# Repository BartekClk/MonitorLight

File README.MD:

# MonitorLight — ATtiny85 Desk Lamp Controller

[-blue?logo=c)](https://www.microchip.com/)
[-lightgrey)](https://www.microchip.com/en-us/product/attiny85)

A compact, hardware desk lamp (screenbar) controller designed for monitor mounting. The project combines dedicated power regulation using a synchronous step-down converter, an incremental rotary encoder UI, and deterministic pure C firmware without Arduino runtime overhead.

---

## Key Features

* **Silent Power Stage (Fast PWM 31.25 kHz):** Operating well above the human audible spectrum (20 Hz – 20 kHz) eliminates inductor whine and ceramic capacitor piezo singing while avoiding camera sensor flicker.
* **Hardware Eye Perception (CIE 1931 Gamma Curve):** 32-step nonlinear lookup table stored in `PROGMEM` providing perceptually uniform brightness adjustments across the entire range.
* **True 0% PWM Standby:** Explicitly disconnects the timer output compare pin when turned off, eliminating residual sub-microsecond voltage spikes typical of AVR Fast PWM and preventing LED glow in standby.
* **Bounce-Immune Quadrature Decoding:** 16-state transition table state machine eliminates mechanical encoder bounce (EC11) without requiring external RC filter networks.
* **EEPROM Wear-Leveling Protection:** Current brightness level is committed to EEPROM only after 2 seconds of inactivity, drastically extending non-volatile cell endurance.
* **Soft-Fade Transition:** Smooth duty cycle ramping during power toggling and manual step adjustments.

---

## Hardware Architecture

| Component | Part / Value | Role in Circuit |
| :--- | :--- | :--- |
| **MCU** | `ATtiny85-20SU` (SOIC-8) | Main microcontroller (8 MHz internal, BOD 2.7V) |
| **Buck Regulator** | `AP63205WU-7` (TSOT-26) | Logic power rail: 12V → 5V (2A, 1.1 MHz) |
| **Switching MOSFET** | `IRLR024N` (TO-252) | Logic-level N-MOSFET Low-Side switch for 12V LED load |
| **Rotary Encoder** | `EC11E20-20P20C-SW` | User interface (20 PPR / 20 detents + momentary push button) |
| **Programming Port** | `J_ISP` (Pin Header) | Dedicated AVR ISP programming header |

### Pinout Configuration

```text
                  ┌───────[ ATtiny85 ]───────┐
      RESET (PB5) │ 1 [•]                  8 │ VCC (+5V AP63205)
   ENC_CLK  (PB3) │ 2                      7 │ PB2 (SCK / Unused)
   ENC_DT   (PB4) │ 3                      6 │ PB1 (ENC_SW - Pushbutton)
              GND │ 4                      5 │ PB0 (PWM -> MOSFET Gate)
                  └──────────────────────────┘
```

---

## Firmware State Machine

```mermaid
stateDiagram-v2
    [*] --> Standby: 12V Power Applied (Default OFF)
    
    Standby --> Active: Push Button (SW)
    note right of Active
      Soft-fade to saved
      brightness from EEPROM
    end note

    Standby --> Active: Rotate Clockwise (CW)
    note left of Standby
      Wake-up from minimum level (1)
    end note

    Active --> Active: Rotate Encoder (Step +/- along CIE1931)
    Active --> Standby: Push Button (SW / Soft-fade to 0)
    
    state Active {
        [*] --> Running
        Running --> EEPROM_Pending: Brightness Changed
        EEPROM_Pending --> Running: Commit after 2s inactivity
    }
```

---

## Repository Structure

```text
MonitorLight/
├── MonitorLight.kicad_sch   # KiCad schematic
├── MonitorLight.kicad_pcb   # Single-layer PCB layout
├── MonitorLight.kicad_pro   # KiCad project file
├── MonitorLight_Code/       # Firmware directory (PlatformIO)
│   ├── src/
│   │   └── main.c           # Pure C firmware (AVR-GCC)
│   ├── diagram.json         # Wokwi simulation circuit configuration
│   ├── wokwi.toml           # Wokwi VS Code integration settings
│   └── platformio.ini       # PlatformIO build configuration & fuse settings
├── .gitignore               # Repository hygiene rules
└── README.md
```

---

## Getting Started & Simulation

### Prerequisites
* [Visual Studio Code](https://code.visualstudio.com/)
* **PlatformIO IDE** extension
* **Wokwi Simulator** extension

### Local Build and Simulation
1. Clone the repository:
   ```bash
   git clone [https://github.com/](https://github.com/)<your-username>/MonitorLight.git
   ```
2. Open the `MonitorLight_Code` directory in VS Code.
3. Build the binary:
   ```bash
   pio run
   ```
4. Open `diagram.json`, open the command palette (`F1`), and execute:
   ```text
   Wokwi: Start Simulator
   ```
   *Rotate the encoder with the mouse, test button presses, and inspect real-time signal waveforms in the generated `wokwi.vcd` trace using extensions like VaporView.*

---

## Hardware Flashing

Flashing the physical board requires a standard **USBasp** programmer connected to the `J_ISP` header:

1. Burn fuse bits (Internal 8 MHz oscillator, BOD enabled at 2.7V):
   ```bash
   pio run -t fuses
   ```
   * Target values: `lfuse: 0xE2`, `hfuse: 0xDD`, `efuse: 0xFF`
2. Upload firmware via ISP:
   ```bash
   pio run -t upload
   ```

---

## License

This project is licensed under the MIT License — see the `LICENSE` file for details.

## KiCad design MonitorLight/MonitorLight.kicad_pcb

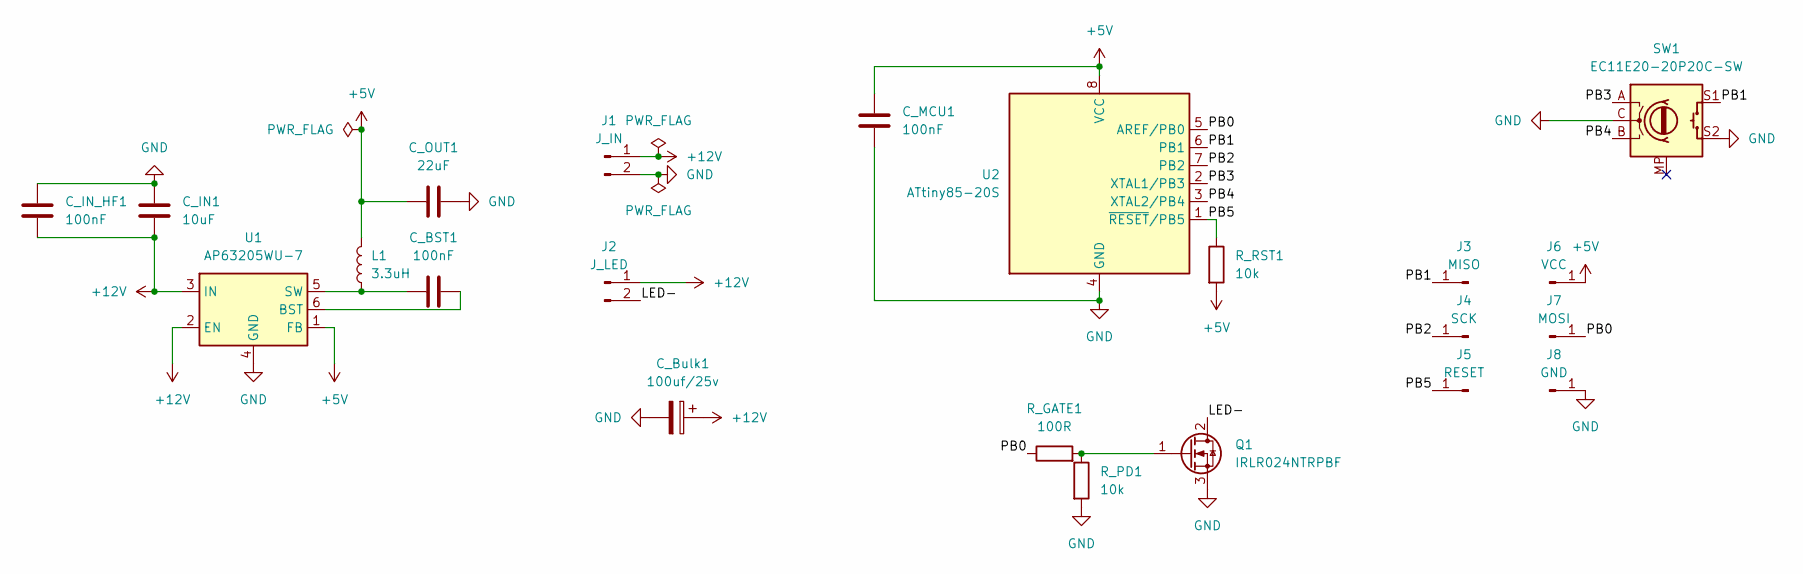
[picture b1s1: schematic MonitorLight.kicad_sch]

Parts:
C_BST1: 100nF; C_0805_2012Metric
C_Bulk1: 100uf/25v; C_Radial_D6.3mm_H11.0mm_P2.50mm
C_IN1: 10uF; C_0805_2012Metric
C_IN_HF1: 100nF; C_0805_2012Metric
C_MCU1: 100nF; C_0805_2012Metric
C_OUT1: 22uF; C_0805_2012Metric
J1: J_IN; SolderPads_01x02_M
J2: J_LED; SolderPads_01x02_M
J3: MISO; InspectionPads_01
J4: SCK; InspectionPads_01
J5: RESET; InspectionPads_01
J6: VCC; InspectionPads_01
J7: MOSI; InspectionPads_01
J8: GND; InspectionPads_01
L1: 3.3uH; L_Taiyo-Yuden_MD-2020
Q1: IRLR024NTRPBF
R_GATE1: 100R; R_0805_2012Metric
R_PD1: 10k; R_0805_2012Metric
R_RST1: 10k; R_0805_2012Metric
SW1: EC11E20-20P20C-SW; RotaryEncoder_Alps_EC11E-Switch_Vertical_H20mm_CircularMoun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
U1: AP63205WU-7; TSOT-23-6
U2: ATtiny85-20S; SOIC-8_5.3x5.3mm_P1.27mm

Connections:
+5V: C_MCU1.1, C_OUT1.1, J6.1 (Pin_1_1), L1.2, R_RST1.2, U1.1 (FB), U2.8 (VCC)
+12V: C_Bulk1.1, C_IN1.2, C_IN_HF1.2, J1.1, J2.1, U1.2 (EN), U1.3 (IN)
/LED-: J2.2, Q1.2 (D)
/PB0: J7.1 (Pin_1_1), R_GATE1.1, U2.5 (AREF/PB0)
/PB1: J3.1 (Pin_1_1), SW1.S1, U2.6 (PB1)
/PB2: J4.1 (Pin_1_1), U2.7 (PB2)
/PB3: SW1.A, U2.2 (XTAL1/PB3)
/PB4: SW1.B, U2.3 (XTAL2/PB4)
/PB5: J5.1 (Pin_1_1), R_RST1.1, U2.1 (~RESET/PB5)
GND: C_Bulk1.2, C_IN1.1, C_IN_HF1.1, C_MCU1.2, C_OUT1.2, J1.2, J8.1 (Pin_1_1), Q1.3 (S), R_PD1.2, SW1.C, SW1.S2, U1.4 (GND), U2.4 (GND)
unnamed: Q1.1 (G), R_GATE1.2, R_PD1.1
unnamed: C_BST1.2, U1.6 (BST)
unnamed: C_BST1.1, L1.1, U1.5 (SW)

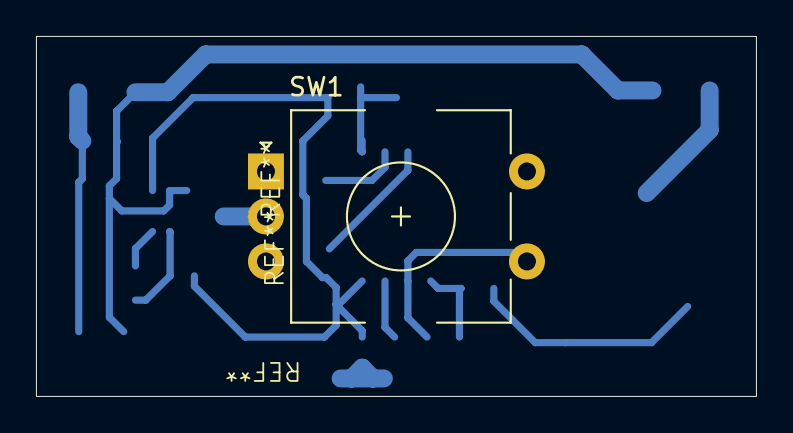
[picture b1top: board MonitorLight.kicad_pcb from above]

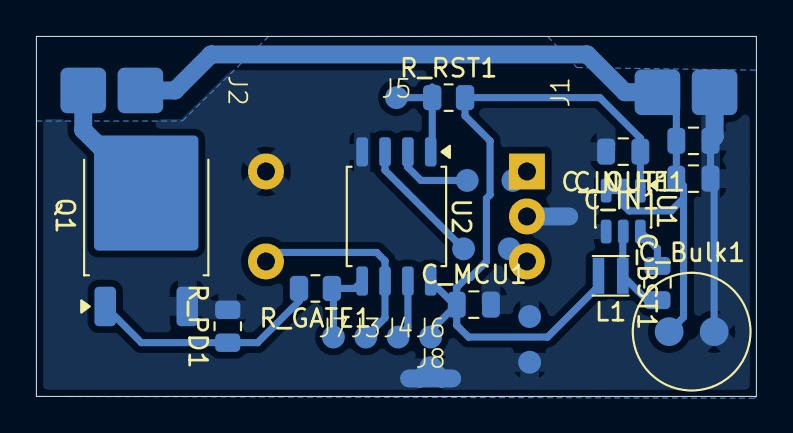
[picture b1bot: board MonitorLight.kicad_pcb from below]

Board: 2 copper layers, 40.0 x 20.0 mm, 22 parts (21 on the bottom side), 13 nets.

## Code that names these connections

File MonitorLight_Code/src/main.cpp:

#define F_CPU 8000000UL

#include <avr/io.h>
#include <avr/interrupt.h>
#include <avr/pgmspace.h>
#include <avr/eeprom.h>
#include <avr/power.h>
#include <stdbool.h>

// --- DEFINICJE PINÓW ---
#define PIN_PWM     PB0  // Pin 5: Wyjście PWM (OC0A)
#define PIN_ENC_SW  PB1  // Pin 6: Przycisk enkodera (SW)
#define PIN_ENC_A   PB3  // Pin 2: Enkoder A (CLK)
#define PIN_ENC_B   PB4  // Pin 3: Enkoder B (DT)

// --- PARAMETRY REGULACJI ---
#define BRIGHTNESS_STEPS 32
#define FADE_INTERVAL_MS 2     // Czas między krokami płynnego przejścia (2 ms)
#define EEPROM_DELAY_MS  2000  // Zapis do EEPROM po 2 s bezczynności

// Tablica korekcji gamma CIE1931 (32 kroki jasności)
static const uint8_t PROGMEM gamma_lut[BRIGHTNESS_STEPS] = {
      1,   2,   3,   4,   6,   8,  10,  13,
     16,  20,  25,  30,  36,  43,  51,  60,
     70,  81,  93, 106, 120, 136, 153, 171,
    190, 210, 232, 255, 255, 255, 255, 255
};

// Tablica przejść kwadraturowych enkodera (eliminuje drgania styków)
static const int8_t PROGMEM enc_table[16] = {
     0, -1,  1,  0,
     1,  0,  0, -1,
    -1,  0,  0,  1,
     0,  1, -1,  0
};

// Adresy EEPROM
#define EEPROM_MAGIC_ADDR 0x00
#define EEPROM_LEVEL_ADDR 0x01
#define EEPROM_MAGIC_KEY  0xA5

// --- ZMIENNE WSPÓŁDZIELONE Z PRZERWANIEM ---
volatile int8_t  g_enc_delta   = 0;
volatile bool    g_btn_pressed = false;
volatile bool    g_tick_1ms    = false;

// --- OBSŁUGA PWM (Timer0 - 31.25 kHz) ---
static void pwm_init(void) {
    DDRB |= (1 << PIN_PWM);
    PORTB &= ~(1 << PIN_PWM);

    // Tryb Fast PWM (WGM01 | WGM00), preskaler = 1 (CS00)
    TCCR0A = (1 << WGM01) | (1 << WGM00);
    TCCR0B = (1 << CS00);
    OCR0A  = 0;
}

static void pwm_set(uint8_t duty) {
    if (duty == 0) {
        // Odłącz wyjście OC0A, aby uniknąć szpilki przy OCR0A = 0
        TCCR0A &= ~(1 << COM0A1);
        PORTB  &= ~(1 << PIN_PWM);
    } else {
        OCR0A   = duty;
        TCCR0A |= (1 << COM0A1);
    }
}

// --- BAZA CZASU 1 ms (Timer1) ---
static void timer1_init(void) {
    // Tryb CTC, preskaler = 64 -> 8 MHz / 64 = 125 kHz
    // 125 impulsów (OCR1C = 124) daje przerwanie dokładnie co 1 ms (1 kHz)
    TCCR1  = (1 << CTC1) | (1 << CS12) | (1 << CS11) | (1 << CS10);
    OCR1C  = 124;
    OCR1A  = 124;
    TIMSK |= (1 << OCIE1A);
}

// --- PRZERWANIE CO 1 ms: ODCZYT ENKODERA I PRZYCISKU ---
ISR(TIMER1_COMPA_vect) {
    g_tick_1ms = true;

    // 1. Dekodowanie kwadraturowe enkodera
    static uint8_t prev_ab    = 0x03;
    static int8_t  substep    = 0;

    uint8_t pin_state = PINB;
    uint8_t curr_ab   = 0;
    if (pin_state & (1 << PIN_ENC_A)) curr_ab |= 0x02;
    if (pin_state & (1 << PIN_ENC_B)) curr_ab |= 0x01;

    if (curr_ab != prev_ab) {
        uint8_t idx = (prev_ab << 2) | curr_ab;
        substep += (int8_t)pgm_read_byte(&enc_table[idx]);
        prev_ab = curr_ab;

        // Zarejestruj krok w pełnej pozycji spoczynkowej (oba wejścia w stanie wysokim)
        if (curr_ab == 0x03) {
            if (substep >= 2) {
                g_enc_delta++;
            } else if (substep <= -2) {
                g_enc_delta--;
            }
            substep = 0;
        }
    }

    // 2. Debouncing przycisku SW (filtr 25 ms)
    static uint8_t btn_cnt     = 0;
    static bool    btn_latched = false;

    if (!(pin_state & (1 << PIN_ENC_SW))) {
        if (btn_cnt < 25) {
            btn_cnt++;
            if (btn_cnt == 25 && !btn_latched) {
                g_btn_pressed = true;
                btn_latched   = true;
            }
        }
    } else {
        btn_cnt     = 0;
        btn_latched = false;
    }
}

// --- PĘTLA GŁÓWNA ---
int main(void) {
    // Wymuś taktowanie 8 MHz (wyłącza podział zegara CKDIV8)
    clock_prescale_set(clock_div_1);

    // Piny enkodera i przycisku jako wejścia z wewnętrznym podciąganiem Pull-Up
    DDRB  &= ~((1 << PIN_ENC_A) | (1 << PIN_ENC_B) | (1 << PIN_ENC_SW));
    PORTB |=  ((1 << PIN_ENC_A) | (1 << PIN_ENC_B) | (1 << PIN_ENC_SW));

    pwm_init();
    timer1_init();
    sei();

    // Odczyt ostatniej jasności z pamięci EEPROM
    uint8_t level = 15; // Domyślnie ~50%
    if (eeprom_read_byte((const uint8_t*)EEPROM_MAGIC_ADDR) == EEPROM_MAGIC_KEY) {
        uint8_t saved = eeprom_read_byte((const uint8_t*)EEPROM_LEVEL_ADDR);
        if (saved < BRIGHTNESS_STEPS) {
            level = saved;
        }
    }

    bool     lamp_on      = false;
    uint8_t  current_pwm  = 0;
    uint8_t  target_pwm   = pgm_read_byte(&gamma_lut[level]);
    uint8_t  fade_timer   = 0;
    uint16_t eeprom_timer = 0;
    bool     eeprom_dirty = false;

    while (1) {
        // 1. Kliknięcie przycisku (włącz / wyłącz)
        if (g_btn_pressed) {
            g_btn_pressed = false;
            lamp_on = !lamp_on;
        }

        // 2. Obrót enkodera (zmiana jasności)
        int8_t delta = 0;
        cli();
        delta = g_enc_delta;
        g_enc_delta = 0;
        sei();

        if (delta != 0) {
            if (!lamp_on && delta > 0) {
                // Obrót w prawo przy wyłączonej lampce włącza ją od minimum
                lamp_on = true;
                level   = 0;
            } else if (lamp_on) {
                int16_t next_level = (int16_t)level + delta;
                if (next_level < 0) next_level = 0;
                if (next_level >= BRIGHTNESS_STEPS) next_level = BRIGHTNESS_STEPS - 1;

                if ((uint8_t)next_level != level) {
                    level        = (uint8_t)next_level;
                    eeprom_dirty = true;
                    eeprom_timer = EEPROM_DELAY_MS;
                }
            }
        }

        // 3. Zadania czasowe wykonywane co 1 ms
        if (g_tick_1ms) {
            g_tick_1ms = false;

            // Wyznaczenie docelowego wypełnienia PWM
            target_pwm = lamp_on ? pgm_read_byte(&gamma_lut[level]) : 0;

            // Płynna zmiana jasności (Soft-Fade) co 2 ms
            fade_timer++;
            if (fade_timer >= FADE_INTERVAL_MS) {
                fade_timer = 0;
                if (current_pwm < target_pwm) {
                    current_pwm++;
                    pwm_set(current_pwm);
                } else if (current_pwm > target_pwm) {
                    current_pwm--;
                    pwm_set(current_pwm);
                }
            }

            // Opóźniony zapis do EEPROM (ochrona przed zużyciem komórek)
            if (eeprom_dirty) {
                if (eeprom_timer > 0) {
                    eeprom_timer--;
                } else {
                    eeprom_update_byte((uint8_t*)EEPROM_MAGIC_ADDR, EEPROM_MAGIC_KEY);
                    eeprom_update_byte((uint8_t*)EEPROM_LEVEL_ADDR, level);
                    eeprom_dirty = false;
                }
            }
        }
    }
}
